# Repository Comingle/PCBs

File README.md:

Comingle PCB Files
======

These files are the design files we use for our circuit boards in our toys. 

Many of the EAGLE files will need the *comingle.lbr* part library, and almost all of the EAGLE files will need the <a href="https://github.com/sparkfun/SparkFun-Eagle-Libraries">Sparkfun Eagle Libraries</a>.

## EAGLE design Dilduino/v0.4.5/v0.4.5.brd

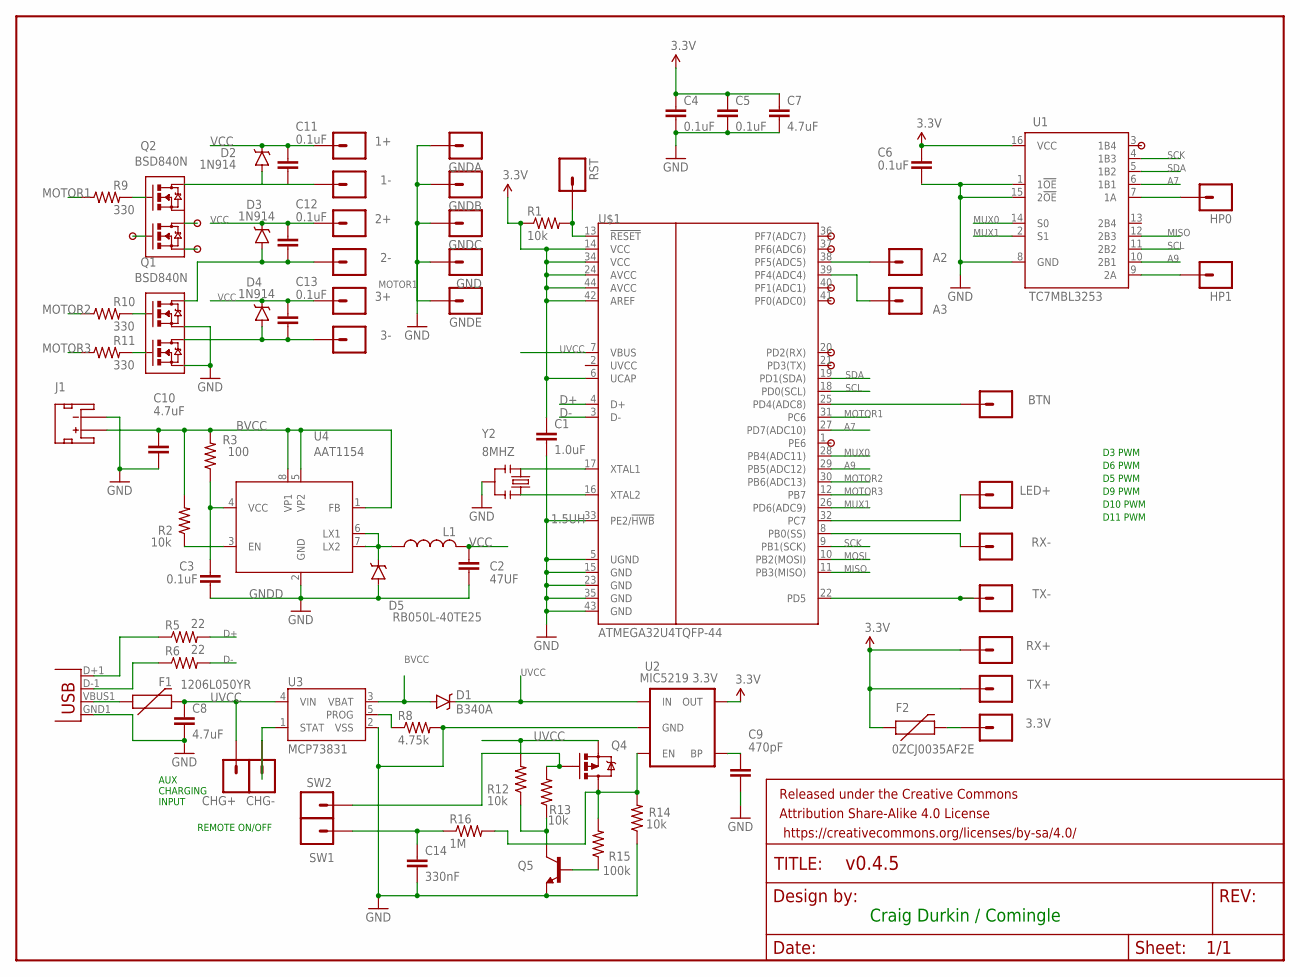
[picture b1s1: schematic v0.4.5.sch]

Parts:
1+, 1-, 2+, 2-, 3+, 3-, 3.3V: M01PTH; 1X01
A2, A3: M01PTH; 1X01
BTN: M01PTH; 1X01
C1: 1.0uF; 0603-CAP
C2: 47UF; 0805
C3, C4, C5, C6, C11, C12, C13: 0.1uF; 0603-CAP
C7: 4.7uF; 0603-CAP
C8, C10: 4.7uF; 1206
C9: 470pF; 0603-CAP
C14: 330nF; 0603-CAP
CHG+: M01PTH; 1X01
CHG-: M01PTH; 1X01
D1: B340A; SMA-DIODE
D2, D3, D4: 1N914; SOD-323
D5: RB050L-40TE25; SMA-DIODE
F1: 1206L050YR; PTC-1206
F2: 0ZCJ0035AF2E; PTC-1206
FRAME1: FRAME-LETTER; CREATIVE_COMMONS
GND: M01PTH; 1X01
GNDA: M01PTH; 1X01
GNDB: M01PTH; 1X01
GNDC: M01PTH; 1X01
GNDE: M01PTH; 1X01
HP0, HP1: M01PTH; 1X01
J1: JST_2MM_MALE; JST-2-SMD
JP4: USB; USB-B-MICRO-SMD_V03
L1: 1.5UH; CHOKE_5MM
LED+: M01PTH; 1X01
PD2, PD3, PD4, PD5, PD6, PD7, PD8, PD9, PD10, PD11, PD12: 040_PAD_030_HOLE; 040_PAD_O30_HOLE
Q1, Q2: BSD840N; PG-SOT-363
Q4: NTS2101PT1G; SOT23-3
Q5: MMBT2222A; SOT23-3
R1, R2, R12, R13, R14: 10k; 0603-RES
R3: 100; 0603-RES
R5, R6: 22; 0603-RES
R8: 4.75k; 0603-RES
R9, R10, R11: 330; 0603-RES
R15: 100k; 0603-RES
R16: 1M; 0603-RES
RST: M01PTH; 1X01
RX+: M01PTH; 1X01
RX-: M01PTH; 1X01
SW1, SW2: M01PTH; 1X01
TX+: M01PTH; 1X01
TX-: M01PTH; 1X01
U1: TC7MBL3253; SSOP16-PRACTICE
U2: MIC5219 3.3V; SOT23-5
U3: MCP73831; SOT23-5
U4: AAT1154; SOP-8
U$1: ATMEGA32U4TQFP-44; TQFP44
Y2: 8MHZ; RESONATOR-SMD

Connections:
A7: U1.6 (1B1), U$1.27 (PD7(ADC10))
A9: U1.10 (2B1), U$1.29 (PB5(ADC12))
BVCC: C10.1, D1.A, J1.2 (+), R2.2, R3.2, U3.3 (VBAT), U4.1 (FB), U4.5 (VP2), U4.8 (VP1)
D+: R5.2, U$1.4 (D+)
D-: R6.2, U$1.3 (D-)
GNDD: C1.2, C2.2, C3.2, C4.2, C5.2, C6.2, C7.2, C8.2, C9.2, C10.2, C14.2, D5.A, GND.1, GNDA.1, GNDB.1, GNDC.1, GNDE.1, J1.1 (-), JP4.GND1 (GND), Q1.1 (S), Q1.4 (S1), Q5.2 (E), R8.2, R14.1, U1.1 (1!OE), U1.8 (GND), U1.15 (2!OE), U2.2 (GND), U3.2 (VSS), U4.2 (GND), U$1.5 (UGND), U$1.15 (GND), U$1.23 (GND), U$1.33 (PE2/!HWB), U$1.35 (GND), U$1.43 (GND), Y2.2
MISO: U1.12 (2B3), U$1.11 (PB3(MISO))
MOSI: U$1.10 (PB2(MOSI))
MOTOR1: R9.1, U$1.31 (PC6)
MOTOR2: R10.1, U$1.30 (PB6(ADC13))
MOTOR3: R11.1, U$1.12 (PB7)
MUX0: U1.14 (S0), U$1.28 (PB4(ADC11))
MUX1: U1.2 (S1), U$1.26 (PD6(ADC9))
unnamed: U$1.17 (XTAL1), Y2.1
unnamed: R8.1, U3.5 (PROG)
unnamed: D5.C, L1.1, U4.6 (LX1), U4.7 (LX2)
unnamed: F1.1, JP4.VBUS1 (VBUS)
unnamed: 3.3V.1, F2.2
unnamed: U$1.16 (XTAL2), Y2.3
unnamed: LED+.1, U$1.32 (PC7)
unnamed: RX-.1, U$1.8 (PB0(SS))
unnamed: TX-.1, U$1.22 (PD5)
unnamed: JP4.D+1 (D+), R5.1
unnamed: JP4.D-1 (D-), R6.1
unnamed: Q4.3 (D), R14.2, R15.2, R16.2, U2.3 (EN)
unnamed: HP1.1, U1.9 (2A)
unnamed: HP0.1, U1.7 (1A)
unnamed: A2.1, U$1.38 (PF5(ADC5))
unnamed: A3.1, U$1.39 (PF4(ADC4))
unnamed: BTN.1, U$1.25 (PD4(ADC8))
unnamed: Q2.2 (G), R9.2
unnamed: CHG-.1, U3.1 (STAT)
unnamed: Q5.3 (C), R12.1, R13.1
unnamed: C14.1, R16.1, SW1.1
unnamed: C9.1, U2.4 (BP)
unnamed: Q4.1 (G), R13.2, SW2.1
unnamed: 1-.1, C11.2, D2.A, Q2.6 (D)
unnamed: 2-.1, C12.2, D3.A, Q1.6 (D)
unnamed: 3-.1, C13.2, D4.A, Q1.3 (D1)
unnamed: PD3.1, U$1.21 (PD3(TX))
unnamed: PD4.1, U$1.20 (PD2(RX))
unnamed: PD5.1, U$1.41 (PF0(ADC0))
unnamed: Q5.1 (B), R15.1
unnamed: R2.1, U4.3 (EN)
unnamed: C3.1, R3.1, U4.4 (VCC)
unnamed: PD6.1, U$1.40 (PF1(ADC1))
unnamed: PD7.1, U$1.37 (PF6(ADC6))
unnamed: PD8.1, U$1.36 (PF7(ADC7))
unnamed: PD9.1, U$1.1 (PE6)
unnamed: PD2.1, U1.3 (1B4)
unnamed: PD10.1, Q2.5 (G1)
unnamed: PD11.1, Q2.4 (S1)
unnamed: PD12.1, Q2.3 (D1)
unnamed: Q1.2 (G), R10.2
unnamed: Q1.5 (G1), R11.2
RST: R1.2, RST.1, U$1.13 (!RESET)
SCK: U1.4 (1B3), U$1.9 (PB1(SCK))
SCL: U1.11 (2B2), U$1.18 (PD0(SCL))
SDA: U1.5 (1B2), U$1.19 (PD1(SDA))
UVCC: C8.1, CHG+.1, D1.C, F1.2, Q4.2 (S), R12.2, U2.1 (IN), U3.4 (VIN), U$1.7 (VBUS)
VCC: 1+.1, 2+.1, 3+.1, C1.1, C2.1, C4.1, C5.1, C6.1, C7.1, C11.1, C12.1, C13.1, D2.C, D3.C, D4.C, F2.1, L1.2, R1.1, RX+.1, TX+.1, U1.16 (VCC), U2.5 (OUT), U$1.6 (UCAP), U$1.14 (VCC), U$1.24 (AVCC), U$1.34 (VCC), U$1.42 (AREF), U$1.44 (AVCC)

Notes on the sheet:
Craig Durkin / Comingle
D3 PWM
D5 PWM
D6 PWM
D9 PWM
D10 PWM
D11 PWM
AUX CHARGING INPUT
REMOTE ON/OFF

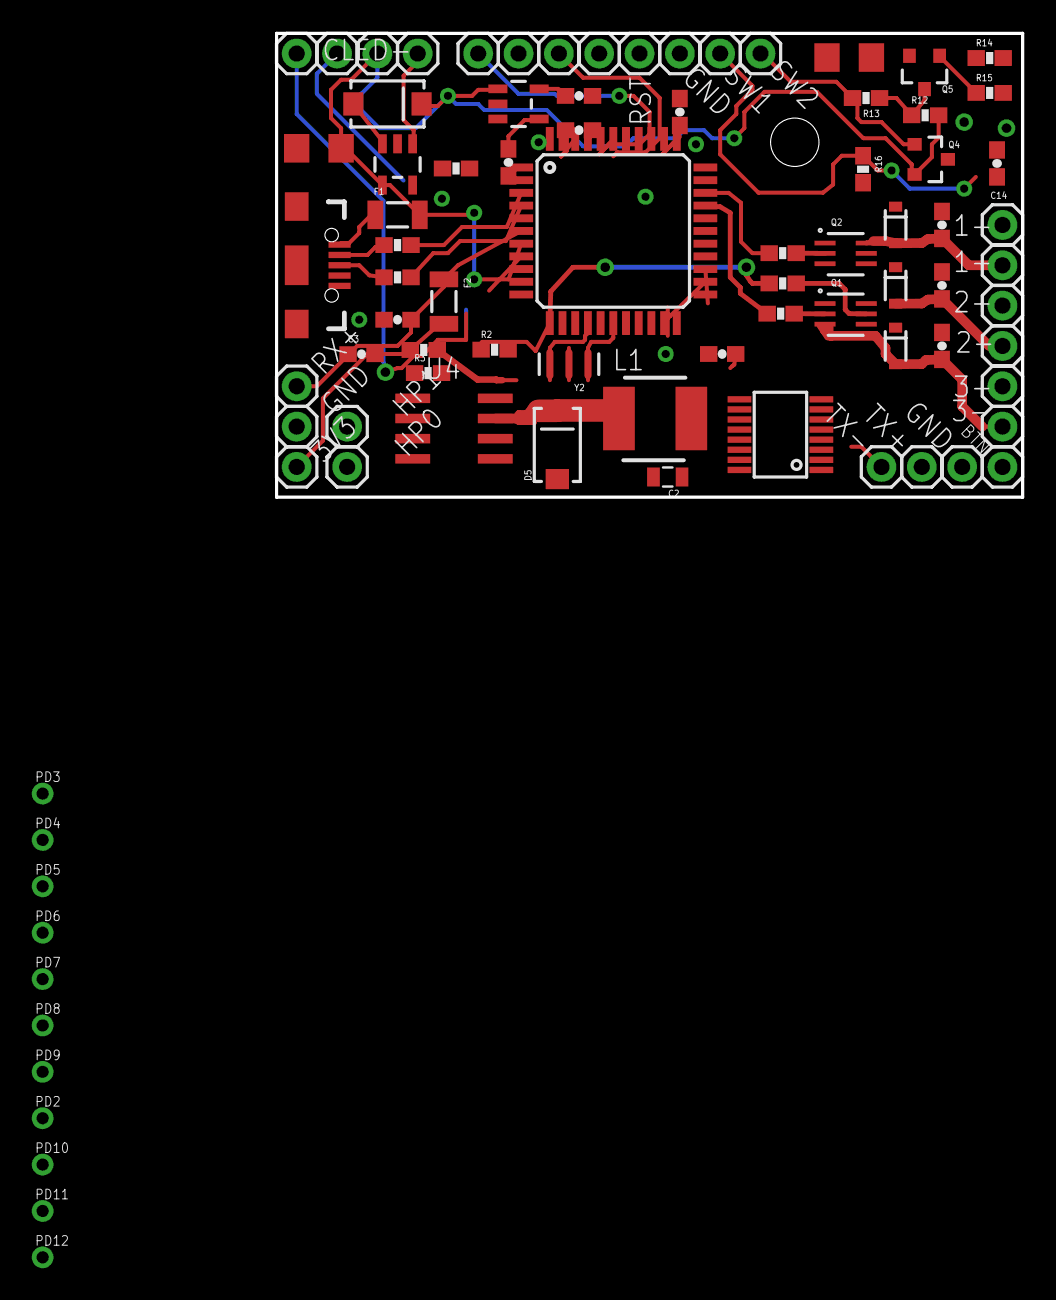
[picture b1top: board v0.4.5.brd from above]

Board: 2 copper layers, 47.0 x 29.2 mm, 88 parts (1 on the bottom side), 60 nets.

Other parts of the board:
U$2: STAND-OFF-TIGHT

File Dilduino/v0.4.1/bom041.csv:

"Qty";"Value";"Device";"Package";"Parts";"Description";"PROD_ID";"VALUE";
"1";"";"JST_2MM_MALE";"JST-2-SMD";"J1";"Mates to single-cell LiPo batteries.";"CONN-08352";"";
"27";"";"M01PTH";"1X01";"1+, 1-, 2+, 2-, 3+, 3-, 3.3V, A2, A3, BTN, CHG+, CHG-, GND, GNDC, GNDE, GNDE1, GNDE2, LED+, OUT1, OUT2, RST, RX+, RX-, SW1, SW2, TX+, TX-";"Header 1";"";"";
"6";"0.1uF";"CAP0603-CAP";"0603-CAP";"C4, C5, C6, C11, C12, C13";"Capacitor";"";"";
"1";"1.0uF";"CAP0603-CAP";"0603-CAP";"C1";"Capacitor";"";"";
"1";"100k";"RESISTOR0603-RES";"0603-RES";"R15";"Resistor";"";"";
"5";"10k";"RESISTOR0603-RES";"0603-RES";"R1, R8, R12, R13, R14";"Resistor";"";"";
"1";"1206L016WR";"PTCSMD";"PTC-1206";"F2";"Resettable Fuse PTC";"RES-11150";"";
"1";"1206L050YR";"PTCSMD";"PTC-1206";"F1";"Resettable Fuse PTC";"RES-11150";"";
"1";"1M";"RESISTOR0603-RES";"0603-RES";"R16";"Resistor";"";"";
"2";"22";"RESISTOR0603-RES";"0603-RES";"R5, R6";"Resistor";"";"";
"2";"22pF";"CAP0603-CAP";"0603-CAP";"C2, C3";"Capacitor";"";"";
"3";"330";"RESISTOR0603-RES";"0603-RES";"R9, R10, R11";"Resistor";"";"";
"1";"330nF";"CAP0603-CAP";"0603-CAP";"C14";"Capacitor";"";"";
"1";"4.7uF";"CAP0603-CAP";"0603-CAP";"C7";"Capacitor";"";"";
"2";"4.7uF";"CAP1206";"1206";"C8, C10";"Capacitor";"";"";
"1";"470pF";"CAP0603-CAP";"0603-CAP";"C9";"Capacitor";"";"";
"1";"74CBTLV3253";"74CBTLV3253";"SSOP16-PRACTICE";"U1";"74CBT 2 x 4:1 multiplexer. 1OE and 2OE are output enable pins, and S0 and S1 determine which ouptut (xB4, xB3, ...) is connected to the xA";"";"";
"1";"8 MHz";"CRYSTAL5X3";"CRYSTAL-SMD-5X3";"Y1";"Various standard crystals. Proven footprints.";"XTAL-08218";"";
"1";"ATMEGA32U4TQFP-44";"ATMEGA32U4TQFP-44";"TQFP44";"U$1";"Atmel 44-pin 8-bit Microcontroller with 32KBytes of ISP Flash and USB Controller";"";"";
"1";"B340A";"DIODE-SCHOTTKY-B340A";"SMA-DIODE";"D1";"Schottky diodes in SFE's production catalog";"DIO-09886";"B340A";
"3";"BAT20JFILM";"BAT20JFILM";"SOD-323";"D2, D3, D4";"23V, 1A Schottky diode, SOD-323 package";"DIO-11623";"BAT20JFILM";
"1";"FRAME-LETTER";"FRAME-LETTER";"CREATIVE_COMMONS";"FRAME1";"Schematic Frame";"";"";
"1";"MCP73831";"MCP73831";"SOT23-5";"U3";"Miniature single cell, fully integrated Li-Ion, Li-polymer charge management controller";"IC-09995";"";
"1";"MIC5219 3.3V";"V_REG_MIC52193.3V";"SOT23-5";"U2";"V_REG MIC5219";"VREG-09872";"MIC5219 3.3V";
"1";"MMBT2222A";"TRANSISTOR_NPNMMBT2222A";"SOT23-3";"Q5";"Generic NPN BJT";"TRANS-08049";"MMBT2222A";
"1";"NTS2101PT1G";"MOSFET-PCHANNEL";"SOT23-3";"Q4";"Generic PMOSFET";"TRANS-08285";"";
"1";"USB";"USB";"USB-B-MICRO-SMD_V03";"JP4";"USB Connectors";"";"";
"3";"ZXTN08400BFFTA";"TRANSISTOR_NPNSOT23-3";"SOT23-3";"Q1, Q2, Q3";"Generic NPN BJT";"TRANS-08049";"";

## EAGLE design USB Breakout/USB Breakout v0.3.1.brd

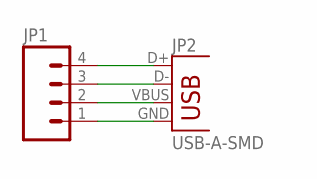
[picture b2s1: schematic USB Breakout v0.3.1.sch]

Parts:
JP1: M04LONGPADS; 1X04_LONGPADS
JP2: USB-A-SMD; USB-A-S-NOSILK-FEMALE

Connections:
3V3: JP1.2, JP2.VBUS
GND: JP1.1, JP2.GND
IN0: JP1.4, JP2.D+
IN1: JP1.3, JP2.D-

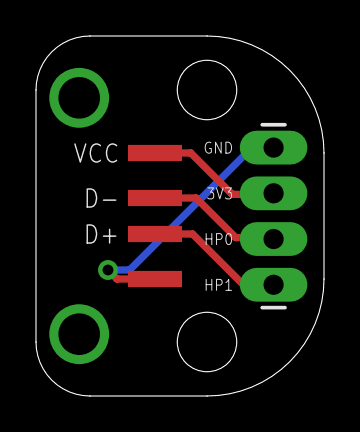
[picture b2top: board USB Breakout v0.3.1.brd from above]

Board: 2 copper layers, 16.0 x 20.0 mm, 4 parts (0 on the bottom side), 4 nets.

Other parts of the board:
U$1, U$2: STAND-OFF

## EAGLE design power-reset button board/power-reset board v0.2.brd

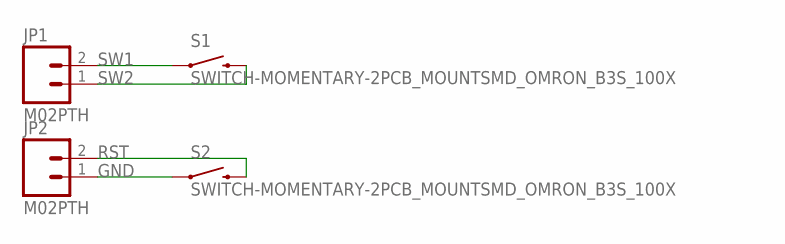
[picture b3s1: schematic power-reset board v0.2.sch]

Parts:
JP1, JP2: M02PTH; 1X02
S1, S2: SWITCH-MOMENTARY-2PCB_MOUNTSMD_OMRON_B3S_100X; TACTILE_SWITCH_LARGE

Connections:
GND: JP2.1, S2.1
RST: JP2.2, S2.3 (2)
SW1: JP1.2, S1.1
SW2: JP1.1, S1.3 (2)

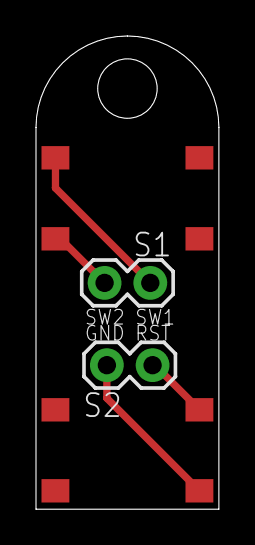
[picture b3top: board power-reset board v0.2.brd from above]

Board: 2 copper layers, 10.2 x 26.3 mm, 5 parts (0 on the bottom side), 4 nets.

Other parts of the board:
U$1: STAND-OFF

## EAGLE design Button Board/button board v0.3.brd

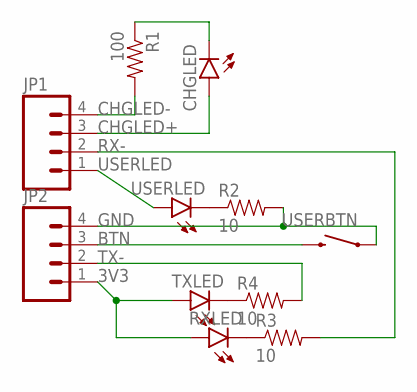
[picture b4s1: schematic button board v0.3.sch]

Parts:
CHGLED: LED-FKIT-1206; FKIT-LED-1206
JP1, JP2: M04PTH; 1X04
R1: 100; 0603-RES
R2, R3, R4: 10; 0603-RES
RXLED: LED-FKIT-1206; FKIT-LED-1206
TXLED: LED-FKIT-1206; FKIT-LED-1206
USERBTN: SWITCH-MOMENTARY-2PCB_MOUNTSMD_OMRON_B3S_100X; TACTILE_SWITCH_LARGE
USERLED: LED-FKIT-1206; FKIT-LED-1206

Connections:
3V3: JP2.1, RXLED.A, TXLED.A
BTN: JP2.3, USERBTN.3 (2), USERBTN.4 (2)
CHGLED+: CHGLED.A, JP1.3
CHGLED-: JP1.4, R1.2
GND: JP2.4, R2.2, USERBTN.1, USERBTN.2 (1)
unnamed: CHGLED.C, R1.1
unnamed: R3.1, RXLED.C
unnamed: R2.1, USERLED.C
unnamed: R4.1, TXLED.C
RX-: JP1.2, R3.2
TX-: JP2.2, R4.2
USERLED: JP1.1, USERLED.A

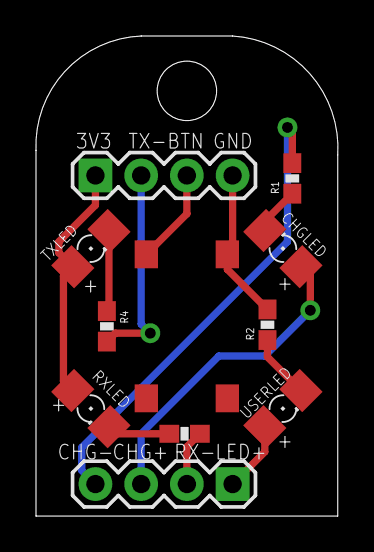
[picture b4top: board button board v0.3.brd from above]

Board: 2 copper layers, 16.8 x 26.7 mm, 12 parts (0 on the bottom side), 12 nets.

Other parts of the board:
U$1: STAND-OFF

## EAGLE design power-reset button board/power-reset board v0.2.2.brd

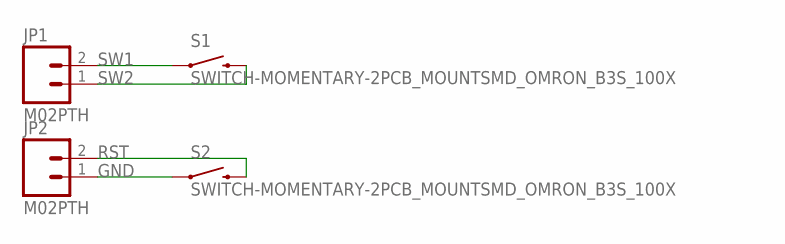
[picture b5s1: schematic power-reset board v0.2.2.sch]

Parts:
JP1, JP2: M02PTH; 1X02
S1, S2: SWITCH-MOMENTARY-2PCB_MOUNTSMD_OMRON_B3S_100X; TACTILE_SWITCH_LARGE

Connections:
GND: JP2.1, S2.1, S2.2 (1)
RST: JP2.2, S2.3 (2), S2.4 (2)
SW1: JP1.2, S1.1, S1.2 (1)
SW2: JP1.1, S1.3 (2), S1.4 (2)

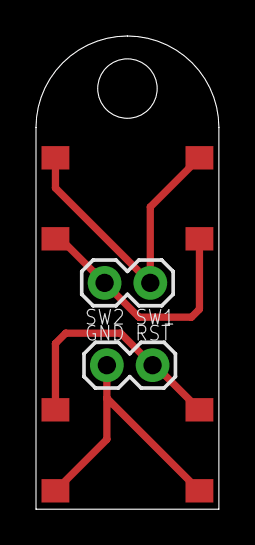
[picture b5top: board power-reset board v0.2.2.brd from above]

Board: 2 copper layers, 10.2 x 26.3 mm, 5 parts (0 on the bottom side), 4 nets.

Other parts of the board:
U$1: STAND-OFF

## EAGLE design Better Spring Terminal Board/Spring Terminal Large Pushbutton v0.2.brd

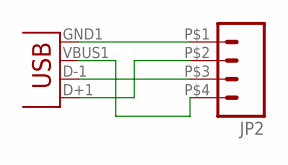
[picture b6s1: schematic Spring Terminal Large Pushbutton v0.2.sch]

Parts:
JP1: USB; USB-B-MICRO-SMD_V03
JP2: M04LARGE_PUSHBTN_SPRING_TERM; 1X04_LARGE_PUSHBTN_SPRING_TERM

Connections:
3V3: JP1.VBUS1 (VBUS), JP2.P$4 (4)
D+: JP1.D+1 (D+), JP2.P$2 (2)
D-: JP1.D-1 (D-), JP2.P$3 (3)
GND: JP1.GND1 (GND), JP2.P$1 (1)

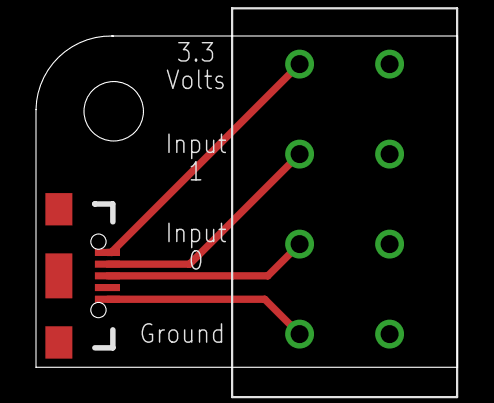
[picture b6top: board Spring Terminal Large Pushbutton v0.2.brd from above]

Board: 2 copper layers, 23.4 x 18.4 mm, 3 parts (0 on the bottom side), 4 nets.

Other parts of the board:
U$1: STAND-OFF

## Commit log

2014-11-14 added motorboard
2016-09-07 finally get the rest our PCBs up

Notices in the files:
parts and their libraries:
SparkFun-Connectors: Licensing: Creative Commons ShareAlike 4.0 International - https://creativecommons.org/licenses/by-sa/4.0
SparkFun-Aesthetics: Released under the Creative Commons Attribution Share-Alike 4.0 License
SparkFun-Aesthetics: https://creativecommons.org/licenses/by-sa/4.0
